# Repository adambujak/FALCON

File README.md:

FALCON

# An attempt at making drone
With Devin Bell ([@devinbellll](https://github.com/devinbellll) - Western University - Mechatronics Engineering) he's working on the flight controller, and I'm doing the RF, hardware, general bringup

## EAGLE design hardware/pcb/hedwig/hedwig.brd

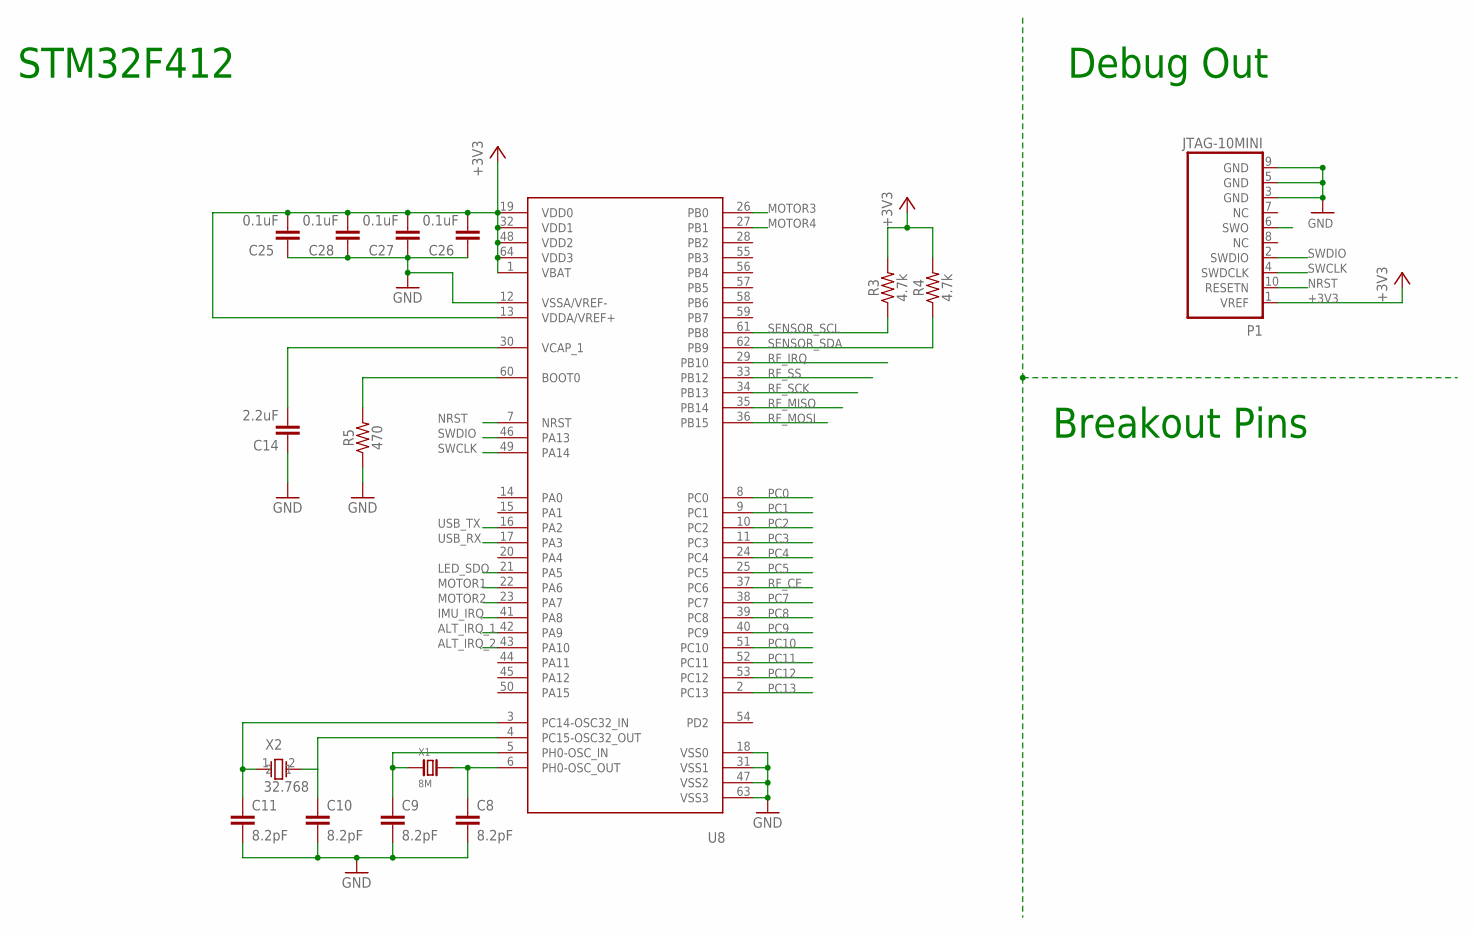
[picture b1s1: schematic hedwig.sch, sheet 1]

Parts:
C8, C9, C10, C11: 8.2pF; 0603
C14: 2.2uF; 0603
C25, C26, C27, C28: 0.1uF; 0603
P1: JTAG-10MINI
R3, R4: 4.7k; 0603
R5: 470; 0603
U8: STM32F412RE-S; QFP50P1200X1200X160-64N
X1: 8M; NDK-NX3225GD
X2: 32.768; NDK_NX3215SA-32.768K-STD-MUA-8_0

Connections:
+3V3: C25.2, C26.2, C27.2, C28.2, P1.1 (VREF), R3.2, R4.2, U8.1 (VBAT), U8.13 (VDDA/VREF+), U8.19 (VDD0), U8.32 (VDD1), U8.48 (VDD2), U8.64 (VDD3); also elsewhere on the board
ALT_IRQ_1: U8.42 (PA9); also elsewhere on the board
ALT_IRQ_2: U8.43 (PA10); also elsewhere on the board
GND: C8.2, C9.2, C10.2, C11.2, C14.1, C25.1, C26.1, C27.1, C28.1, P1.3 (GND), P1.5 (GND), P1.9 (GND), R5.1, U8.12 (VSSA/VREF-), U8.18 (VSS0), U8.31 (VSS1), U8.47 (VSS2), U8.63 (VSS3); also elsewhere on the board
IMU_IRQ: U8.41 (PA8); also elsewhere on the board
LED_SDO: U8.21 (PA5); also elsewhere on the board
MOTOR1: U8.22 (PA6); also elsewhere on the board
MOTOR2: U8.23 (PA7); also elsewhere on the board
MOTOR3: U8.26 (PB0); also elsewhere on the board
MOTOR4: U8.27 (PB1); also elsewhere on the board
unnamed: C9.1, U8.5 (PH0-OSC_IN), X1.1
unnamed: C8.1, U8.6 (PH0-OSC_OUT), X1.2
unnamed: C11.1, U8.3 (PC14-OSC32_IN), X2.1
unnamed: C10.1, U8.4 (PC15-OSC32_OUT), X2.2
unnamed: R5.2, U8.60 (BOOT0)
unnamed: C14.2, U8.30 (VCAP_1)
NRST: P1.10 (RESETN), U8.7 (NRST); also elsewhere on the board
PC0: U8.8 (PC0)
PC1: U8.9 (PC1)
PC2: U8.10 (PC2)
PC3: U8.11 (PC3)
PC4: U8.24 (PC4)
PC5: U8.25 (PC5)
PC7: U8.38 (PC7)
PC8: U8.39 (PC8)
PC9: U8.40 (PC9)
PC10: U8.51 (PC10)
PC11: U8.52 (PC11)
PC12: U8.53 (PC12)
PC13: U8.2 (PC13)
RF_CE: U8.37 (PC6); also elsewhere on the board
RF_IRQ: U8.29 (PB10); also elsewhere on the board
RF_MISO: U8.35 (PB14); also elsewhere on the board
RF_MOSI: U8.36 (PB15); also elsewhere on the board
RF_SCK: U8.34 (PB13); also elsewhere on the board
RF_SS: U8.33 (PB12); also elsewhere on the board
SENSOR_SCL: R3.1, U8.61 (PB8); also elsewhere on the board
SENSOR_SDA: R4.1, U8.62 (PB9); also elsewhere on the board
SWCLK: P1.4 (SWDCLK), U8.49 (PA14)
SWDIO: P1.2 (SWDIO), U8.46 (PA13)
USB_RX: U8.17 (PA3); also elsewhere on the board
USB_TX: U8.16 (PA2); also elsewhere on the board

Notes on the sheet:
Breakout Pins
STM32F412
Debug Out

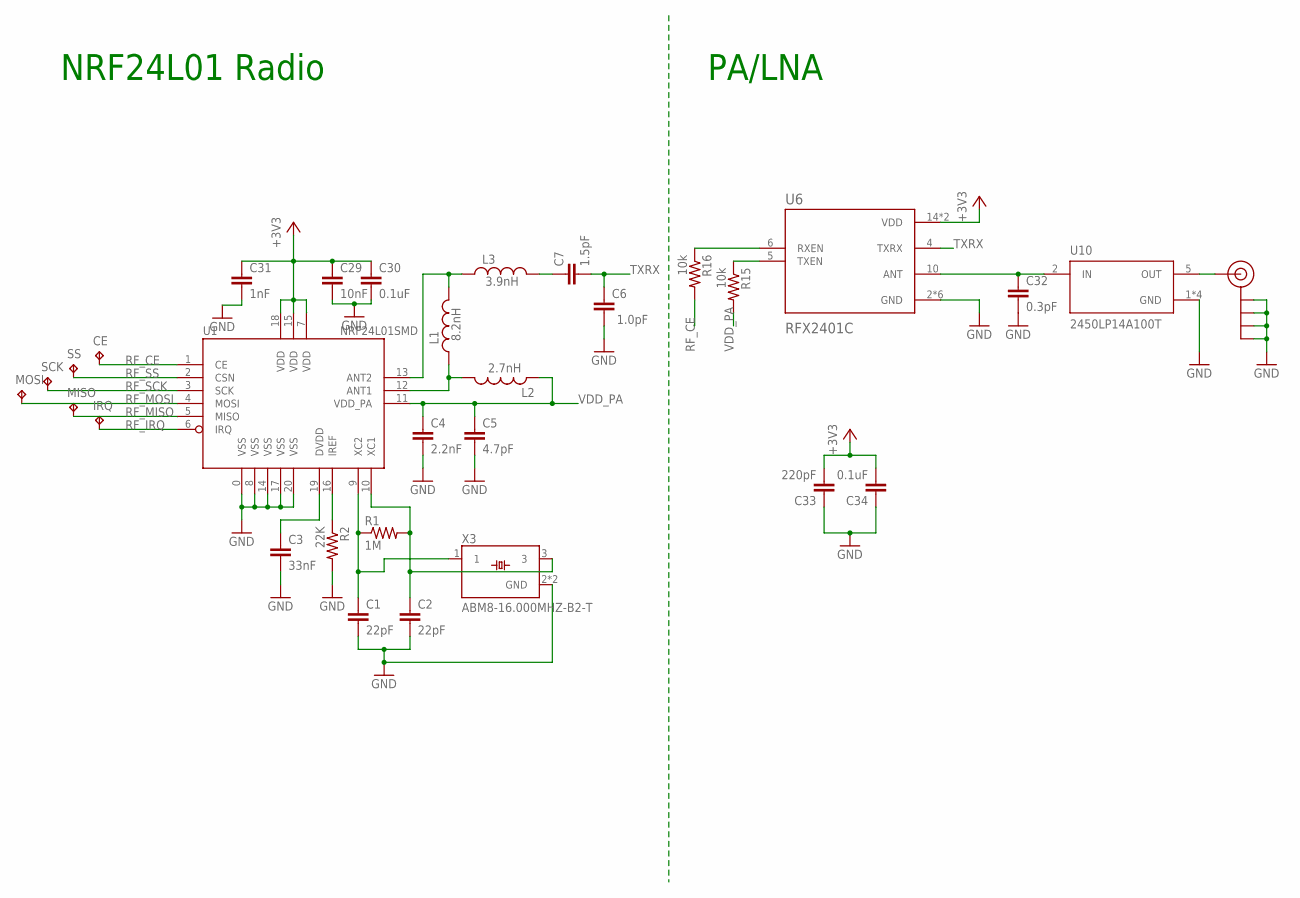
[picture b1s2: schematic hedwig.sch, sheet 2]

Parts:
C1, C2: 22pF; C0402
C3: 33nF; C0402
C4: 2.2nF; C0402
C5: 4.7pF; C0402
C6: 1.0pF; C0402
C7: 1.5pF; C0402
C29: 10nF; C0402
C30, C34: 0.1uF; C0402
C31: 1nF; C0402
C32: 0.3pF; C0402
C33: 220pF; C0402
CE: TPB1,27; B1,27
IRQ: TPB1,27; B1,27
J3: SMA_EDGE; SMA-EDGE
L1: 8.2nH; C0402
L2: 2.7nH; C0402
L3: 3.9nH; C0402
MISO: TPB1,27; B1,27
MOSI: TPB1,27; B1,27
R1: 1M; C0402
R2: 22K; C0402
R15, R16: 10k; C0402
SCK: TPB1,27; B1,27
SS: TPB1,27; B1,27
U1: NRF24L01SMD; QFN20
U6: RFX2401C; QFN50P300X300X60-17N
U10: 2450LP14A100T; ICCAF50P160X80X70-6N
X3: ABM8-16.000MHZ-B2-T; OSCSC320X250X100N

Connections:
+3V3: C29.1, C30.1, C31.1, C33.2, C34.2, U1.7 (VDD), U1.15 (VDD), U1.18 (VDD), U6.14 (VDD), U6.16 (VDD); also elsewhere on the board
GND: C1.2, C2.2, C3.2, C4.2, C5.2, C6.1, C29.2, C30.2, C31.2, C32.2, C33.1, C34.1, J3.GND@0 (GND), J3.GND@1 (GND), J3.GND@2 (GND), J3.GND@3 (GND), R2.2, U1.0 (VSS), U1.8 (VSS), U1.14 (VSS), U1.17 (VSS), U1.20 (VSS), U6.2 (GND), U6.3 (GND), U6.8 (GND), U6.9 (GND), U6.11 (GND), U6.17 (GND), U10.1 (GND), U10.3 (GND), U10.4 (GND), U10.6 (GND), X3.2 (GND), X3.4 (GND); also elsewhere on the board
unnamed: C1.1, R1.1, U1.9 (XC2), X3.1
unnamed: C2.1, R1.2, U1.10 (XC1), X3.3
unnamed: L1.1, L2.2, U1.12 (ANT1)
unnamed: R2.1, U1.16 (IREF)
unnamed: C3.1, U1.19 (DVDD)
unnamed: L1.2, L3.1, U1.13 (ANT2)
unnamed: C7.1, L3.2
unnamed: C32.1, U6.10 (ANT), U10.2 (IN)
unnamed: J3.SIG (SIGNAL), U10.5 (OUT)
unnamed: R16.1, U6.6 (RXEN)
unnamed: R15.1, U6.5 (TXEN)
RF_CE: CE.TP, R16.2, U1.1 (CE); also elsewhere on the board
RF_IRQ: IRQ.TP, U1.6 (IRQ); also elsewhere on the board
RF_MISO: MISO.TP, U1.5 (MISO); also elsewhere on the board
RF_MOSI: MOSI.TP, U1.4 (MOSI); also elsewhere on the board
RF_SCK: SCK.TP, U1.3 (SCK); also elsewhere on the board
RF_SS: SS.TP, U1.2 (CSN); also elsewhere on the board
TXRX: C6.2, C7.2, U6.4 (TXRX)
VDD_PA: C4.1, C5.1, L2.1, R15.2, U1.11 (VDD_PA)

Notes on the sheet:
NRF24L01 Radio
PA/LNA

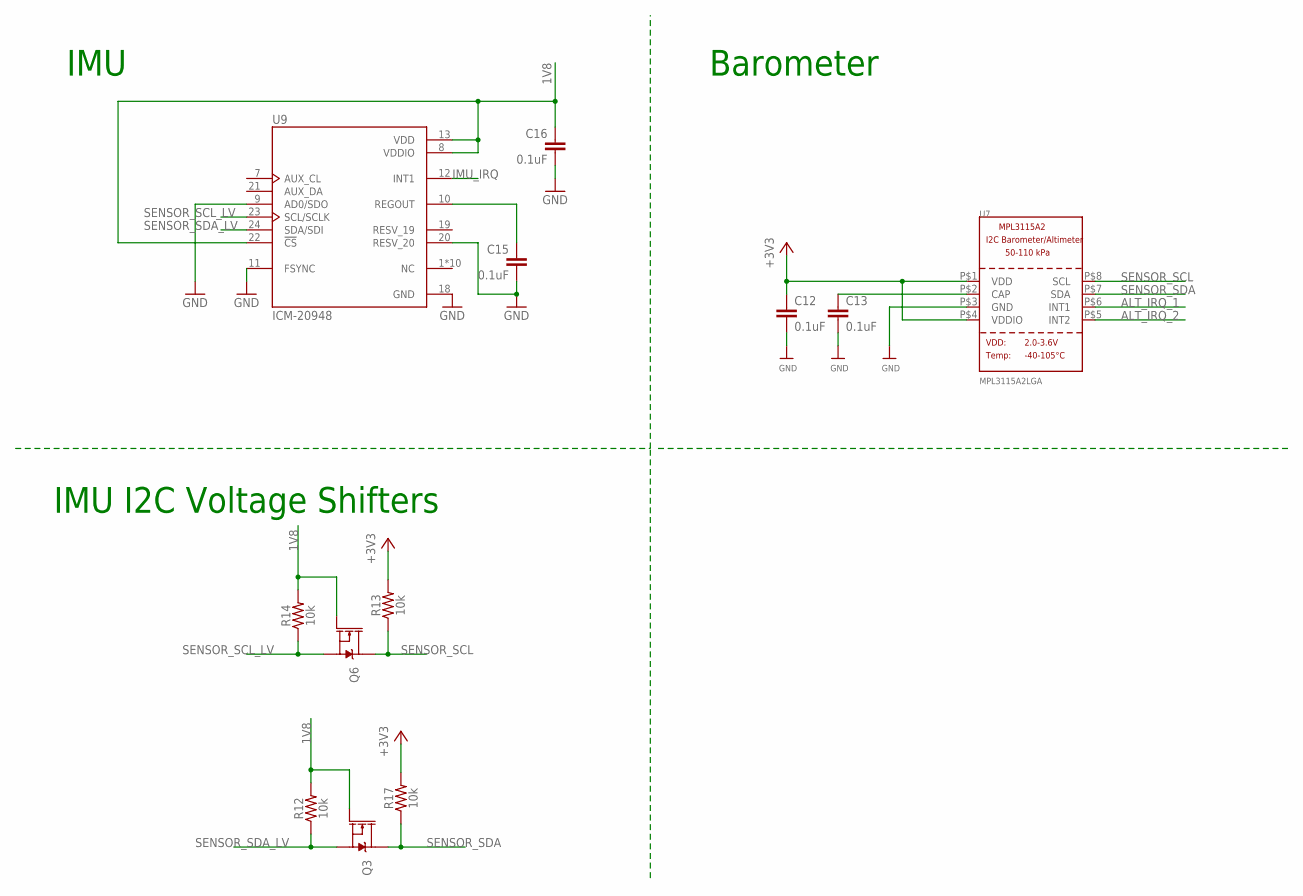
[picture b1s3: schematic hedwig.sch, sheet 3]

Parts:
C12, C13: 0.1uF; 0603
C15, C16: 0.1uF; 0603-CAP
Q3, Q6: 20V/0.2A/8MHz/1.2Ω/1Vth; SOT-416FL
R12, R13, R14, R17: 10k; 0603
U7: MPL3115A2LGA; LGA8
U9: ICM-20948; QFN40P300X300X105-24N

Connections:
1V8: C16.1, Q3.1 (G), Q6.1 (G), R12.2, R14.2, U9.8 (VDDIO), U9.13 (VDD), U9.22 (!CS); also elsewhere on the board
+3V3: C12.1, R13.2, R17.2, U7.P$1 (VDD), U7.P$4 (VDDIO); also elsewhere on the board
ALT_IRQ_1: U7.P$6 (INT1); also elsewhere on the board
ALT_IRQ_2: U7.P$5 (INT2); also elsewhere on the board
CAP: C13.1, U7.P$2 (CAP)
GND: C12.2, C13.2, C15.2, C16.2, U7.P$3 (GND), U9.9 (AD0/SDO), U9.11 (FSYNC), U9.18 (GND), U9.20 (RESV_20); also elsewhere on the board
IMU_IRQ: U9.12 (INT1); also elsewhere on the board
unnamed: C15.1, U9.10 (REGOUT)
SENSOR_SCL: Q6.3 (D), R13.1, U7.P$8 (SCL); also elsewhere on the board
SENSOR_SCL_LV: Q6.2 (S), R14.1, U9.23 (SCL/SCLK)
SENSOR_SDA: Q3.3 (D), R17.1, U7.P$7 (SDA); also elsewhere on the board
SENSOR_SDA_LV: Q3.2 (S), R12.1, U9.24 (SDA/SDI)

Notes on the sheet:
IMU
Barometer
IMU I2C Voltage Shifters

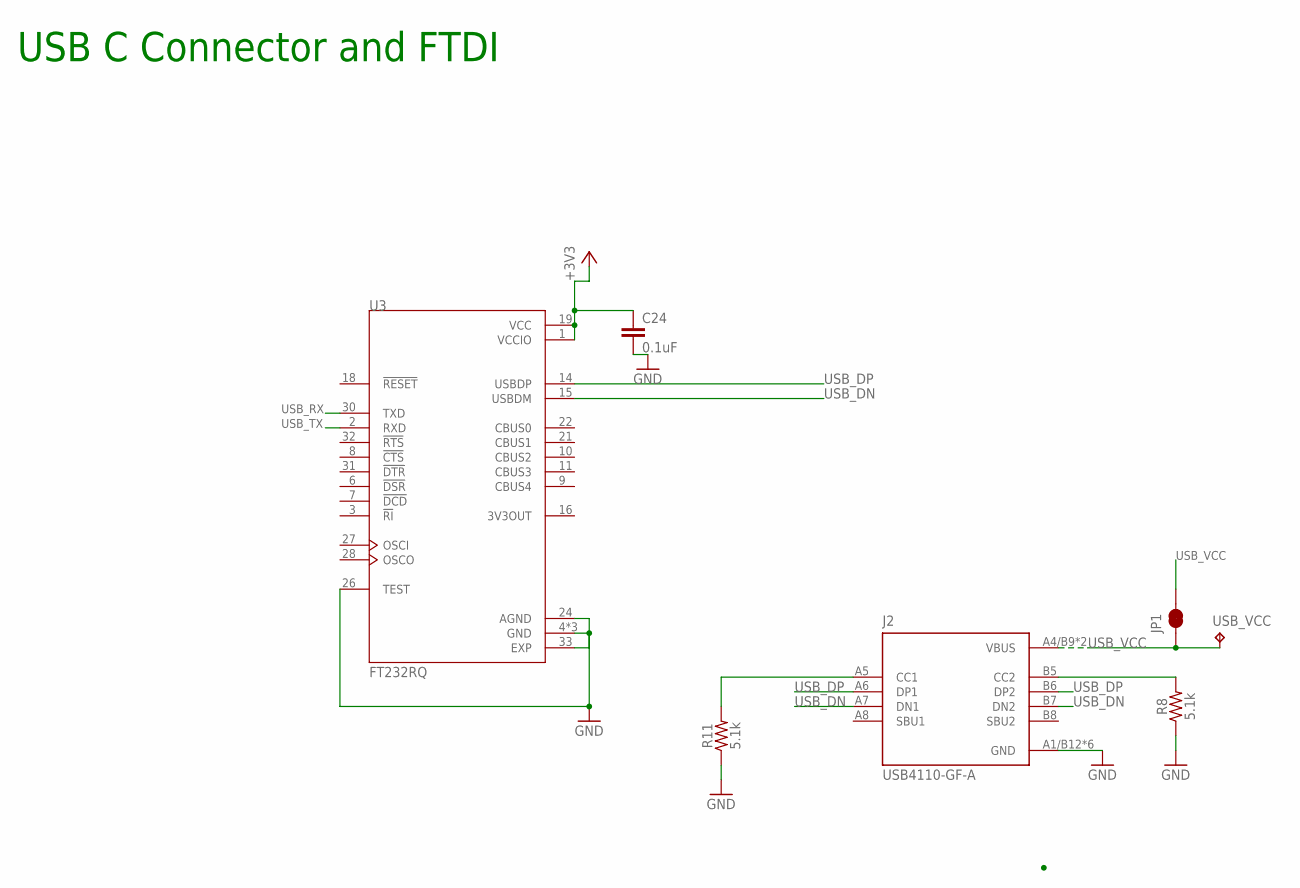
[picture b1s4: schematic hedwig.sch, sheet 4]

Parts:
C24: 0.1uF; 0603
J2: USB4110-GF-A; GCT_USB4110-GF-A
JP1: JUMPER-SMT_2_NC_TRACE_SILK; SMT-JUMPER_2_NC_TRACE_SILK
R8, R11: 5.1k; 0603
U3: FT232RQ; QFN50P500X500X90-33N
USB_VCC: TPB2,54; B2,54

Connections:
+3V3: C24.1, U3.1 (VCCIO), U3.19 (VCC); also elsewhere on the board
GND: C24.2, J2.A1/B12 (GND), J2.B1/A12 (GND), J2.S1 (GND), J2.S2 (GND), J2.S3 (GND), J2.S4 (GND), R8.1, R11.1, U3.4 (GND), U3.17 (GND), U3.20 (GND), U3.24 (AGND), U3.26 (TEST), U3.33 (EXP); also elsewhere on the board
unnamed: J2.B5 (CC2), R8.2
unnamed: J2.A5 (CC1), R11.2
USB_DN: J2.A7 (DN1), J2.B7 (DN2), U3.15 (USBDM)
USB_DP: J2.A6 (DP1), J2.B6 (DP2), U3.14 (USBDP)
USB_RX: U3.30 (TXD); also elsewhere on the board
USB_TX: U3.2 (RXD); also elsewhere on the board
USB_VCC: J2.A4/B9 (VBUS), J2.B4/A9 (VBUS), JP1.1, JP1.2, USB_VCC.TP; also elsewhere on the board

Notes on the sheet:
USB C Connector and FTDI

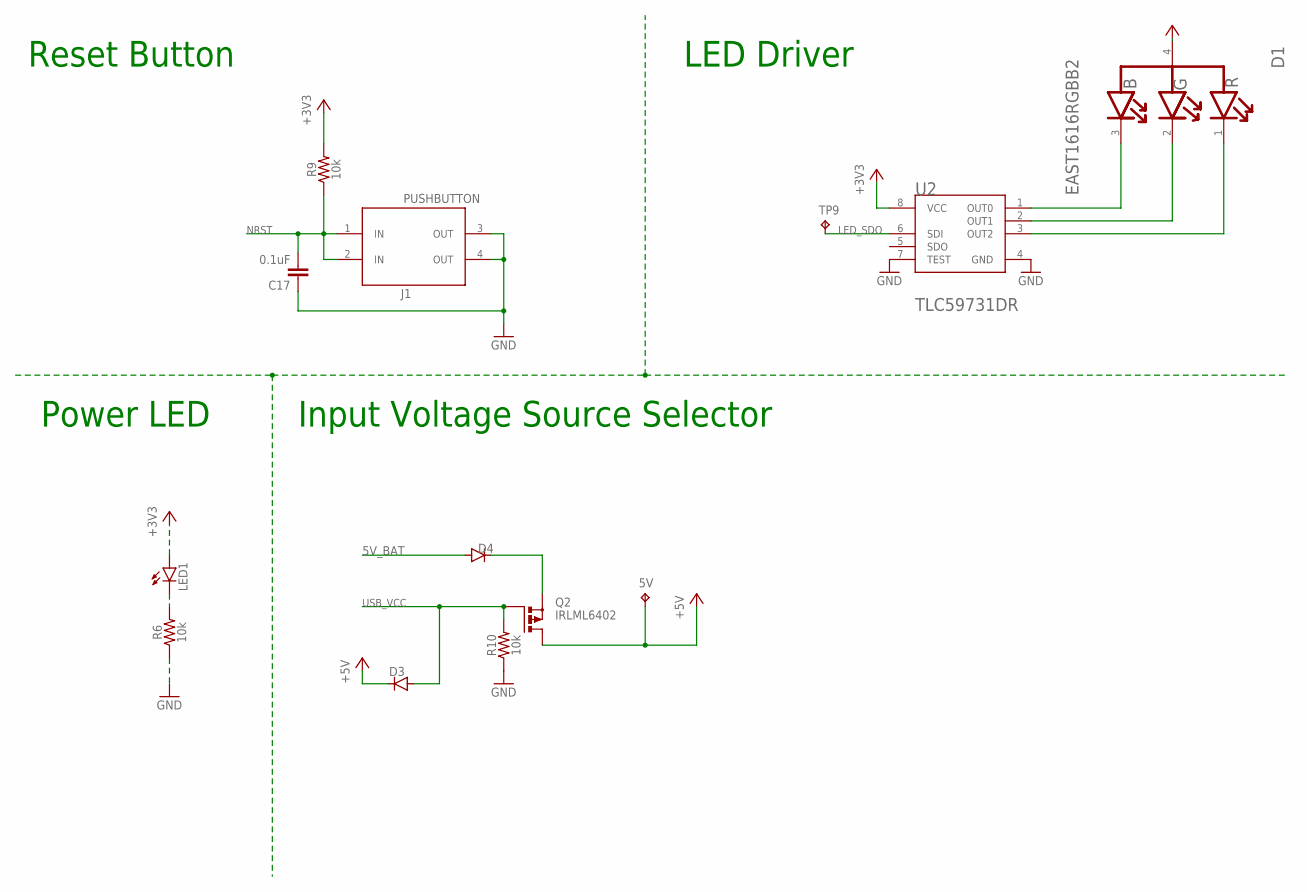
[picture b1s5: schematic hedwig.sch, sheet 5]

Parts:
5V: TPB2,54; B2,54
C17: 0.1uF; 0603
D1: EVERLIGHT_EAST1616RGBB2EVERLIGHT_EAST1616RGBB2_0_0; EVERLIGHT_EAST1616RGBB2_0
D3, D4: DIODE_0603
J1: PUSHBUTTON; PUSH_BUTTON
LED1: LEDCHIPLED_1206; CHIPLED_1206
Q2: IRLML6402; SOT-23
R6, R9, R10: 10k; 0603
TP9: TPB1,27; B1,27
U2: TEXAS_INSTRUMENTS_TLC59731DRTEXAS_INSTRUMENTS_TLC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; TEXAS_INSTRUMENTS_TLC59731DR_0

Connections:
5V_BAT: D4.A; also elsewhere on the board
+3V3: D1.4 (COMMON_ANODE), LED1.A, R9.2, U2.8 (VCC); also elsewhere on the board
+5V: 5V.TP, D3.C, Q2.P3 (D); also elsewhere on the board
GND: C17.1, J1.3 (OUT), J1.4 (OUT), R6.1, R10.1, U2.4 (GND), U2.7 (TEST); also elsewhere on the board
LED_SDO: TP9.TP, U2.6 (SDI); also elsewhere on the board
unnamed: D1.1 (RED_CATHODE), U2.3 (OUT2)
unnamed: D1.3 (BLUE_CATHODE), U2.1 (OUT0)
unnamed: LED1.C, R6.2
unnamed: D1.2 (GREEN_CATHODE), U2.2 (OUT1)
unnamed: D4.C, Q2.P2 (S)
NRST: C17.2, J1.1 (IN), J1.2 (IN), R9.1; also elsewhere on the board
USB_VCC: D3.A, Q2.P1 (G), R10.2; also elsewhere on the board

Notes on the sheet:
Reset Button
LED Driver
Power LED
Input Voltage Source Selector

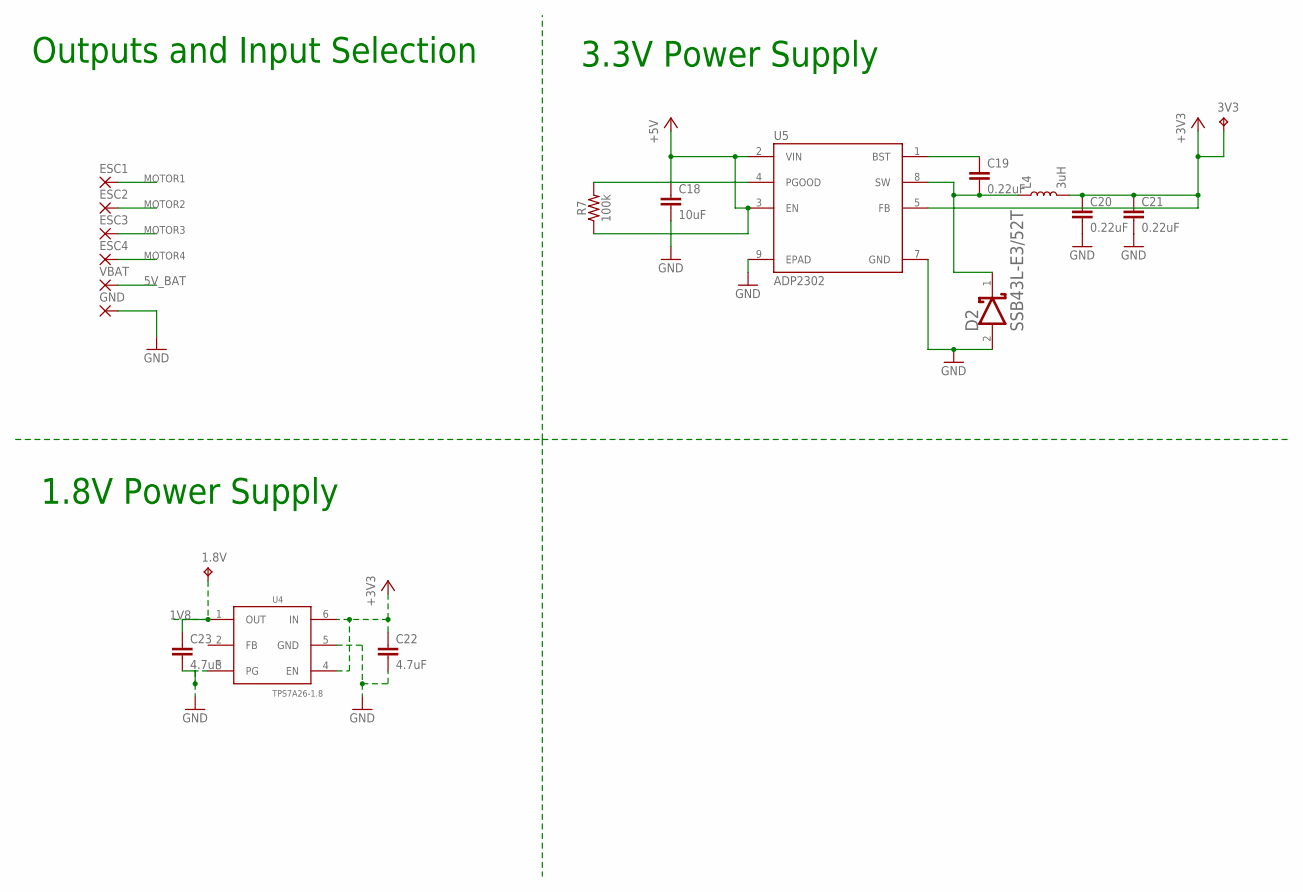
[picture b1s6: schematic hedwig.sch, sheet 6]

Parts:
1.8V, 3V3: TPB2,54; B2,54
C18: 10uF; 0603
C19, C20, C21: 0.22uF; 0603
C22, C23: 4.7uF; 0603
D2: SSB43L; VISHAY_SSB43L-E3-52T_0
ESC1, ESC2, ESC3, ESC4: SMD2; SMD1,27-2,54
GND: 2,54/1,0
L4: 3uH; REG_INDUCTOR
R7: 100k; 0603
U4: TPS7A26-1.8; WSON
U5: ADP2302; SOIC127P600X175-9N
VBAT: 2,54/1,0

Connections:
1V8: 1.8V.TP, C23.1, U4.1 (OUT); also elsewhere on the board
5V_BAT: VBAT.1; also elsewhere on the board
+3V3: 3V3.TP, C20.1, C21.1, C22.1, L4.@2 (2), U4.4 (EN), U4.6 (IN), U5.5 (FB); also elsewhere on the board
+5V: C18.1, R7.1, U5.2 (VIN), U5.3 (EN); also elsewhere on the board
GND: C18.2, C20.2, C21.2, C22.2, C23.2, D2.2 (ANODE), GND.1, U4.3 (PG), U4.5 (GND), U5.7 (GND), U5.9 (EPAD); also elsewhere on the board
MOTOR1: ESC1.1; also elsewhere on the board
MOTOR2: ESC2.1; also elsewhere on the board
MOTOR3: ESC3.1; also elsewhere on the board
MOTOR4: ESC4.1; also elsewhere on the board
unnamed: C19.1, U5.1 (BST)
unnamed: R7.2, U5.4 (PGOOD)
unnamed: C19.2, D2.1 (CATHODE), L4.@1 (1), U5.8 (SW)

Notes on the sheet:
Outputs and Input Selection
3.3V Power Supply
1.8V Power Supply

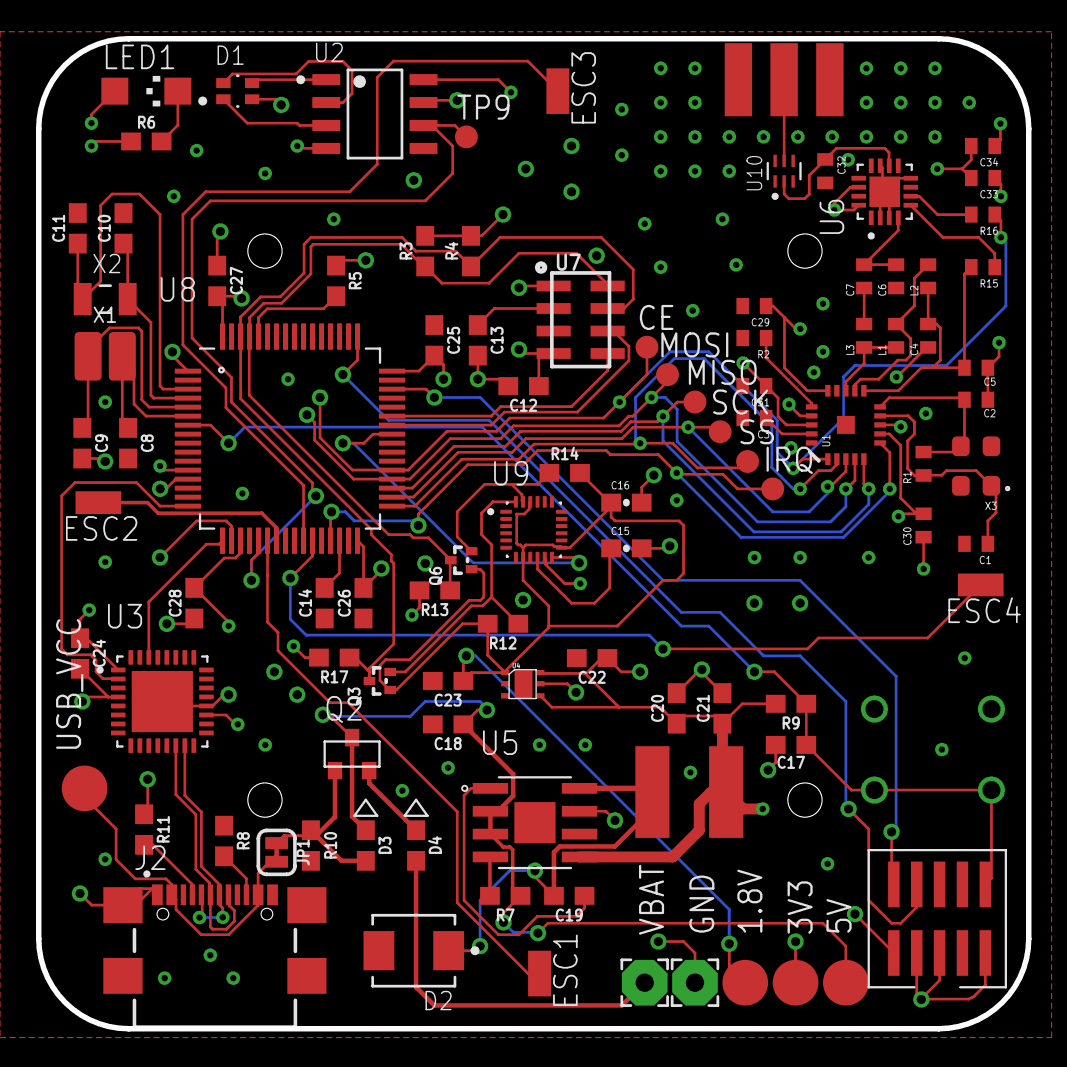
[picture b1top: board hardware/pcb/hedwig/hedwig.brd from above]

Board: 4 copper layers, 55.0 x 55.0 mm, 98 parts (0 on the bottom side), 62 nets.

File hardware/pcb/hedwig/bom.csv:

Parts,Device,Package,Value,Quantity,Digi-Key Part Number
"C1, C2",CAPACITOR,0402,22pF,2,720-1593-1-ND
"C12, C13, C15, C16, C17, C25, C26, C27, C28",CAPACITOR,0603,0.1uF,2,1276-6985-1-ND
C14,CAPACITOR,0603,2.2uF,1,1276-6726-1-ND
C18,CAPACITOR,0603,10uF,1,490-10475-1-ND
"C19, C20, C21",CAPACITOR,0603,0.22uF,3,311-3103-1-ND
"C22, C23",CAPACITOR,0603,4.7uF,2,445-13231-1-ND
C24,CAPACITOR,0603,0.1uF,1,445-13231-1-ND
C29,CAPACITOR,0402,10nF,1,1276-1051-1-ND
C3,CAPACITOR,0402,33nF,1,490-11149-1-ND
"C30, C34",CAPACITOR,0402,0.1uF,2,587-1994-1-ND
C31,CAPACITOR,0402,1nF,1,587-1051-1-ND
C32,CAPACITOR,0402,0.3pF,1,399-6155-1-ND
C33,CAPACITOR,0402,220pF,1,311-3060-1-ND
C4,CAPACITOR,0402,2.2nF,1,587-4324-1-ND
C5,CAPACITOR,0402,4.7pF,1,1276-6694-1-ND
C6,CAPACITOR,0402,1.0pF,1,587-5103-1-ND
C7,CAPACITOR,0402,1.5pF,1,587-5122-1-ND
"C8, C9, C10, C11",CAPACITOR,0603,8.2pF,4,490-12727-1-ND
D1,EVERLIGHT_EAST1616RGBB2EVERLIGHT_EAST1616RGBB2_0_0,CUSTOM,,1,1080-1551-1-ND
D2,VISHAY_SSB43L-E3-52TVISHAY_SSB43L-E3-52T_0_0,CUSTOM,,1,SSB43L-E3/52TGICT-ND
"D3, D4",DIODE_0603,0603,,2,CCS15S30L3FCT-ND
J1,PUSHBUTTON,CUSTOM,,1,2449-CT11025.0F160-ND
J2,USB4110-GF-A,CUSTOM,,1,2073-USB4110-GF-A-1-ND
J3,SMA_EDGE,SMA_EDGE,,1,CONREVSMA003.062-G-ND
L1,INDUCTOR0402,0402,8.2nH,1,2035-0402HP-8N2EHTSCT-ND
L2,INDUCTOR0402,0402,2.7nH,1,2035-0402HP-2N7EDTSCT-ND
L3,INDUCTOR0402,0402,3.9nH,1,2035-0402HP-3N9EDTSCT-ND
L4,INDUCTOR3V3,CUSTOM,3uH,1,445-173052-1-ND
LED1,LEDCHIPLED_1206,1206,,1,MP-3014-1100-35-80
P1,JTAG-10MINI,JTAG-10MINI,,1,SAM8799-ND
Q2,MOSFTET-PCH-IRLML6402,SOT-23,,1,SI2305-TPMSCT-ND
"Q3, Q6",MOSFET-NCH-RE1C002UN,SOT-416FL,,2,RE1C002UNTCLCT-ND
R1,RESISTOR,0402,1M,1,2037-PFR05S-105-FNHCT-ND
"R6, R9, R10, R12, R13, R14, R17",RESISTOR,0603,10k,5,RNCP0603FTD10K0CT-ND
"R15, R16",RESISTOR,0402,10k,2,RNCF0402BTE10K0CT-ND
R2,RESISTOR,0402,22K,1,RMCF0402FT22K0CT-ND
"R3, R4",RESISTOR,0603,4.7k,2,MCT0603-4.7K-MDCT-ND
R5,RESISTOR,0603,470,1,RMCF0603FT470RCT-ND
R7,RESISTOR,0603,100k,1,RMCF0603FT100KCT-ND
"R8, R11",RESISTOR,0603,5.1k,2,RMCF0603FT5K10CT-ND
U1,NRF24L01SMD,QFN20,,1,1490-NRF24L01P-RCT-ND
U2,TLC59731DR,,,1,296-40590-1-ND
U3,FT232RQ,QFN50-33N,,1,768-1307-ND
U4,TPS7A26-1.8,WSON,,1,296-TPS7A2618DRVRCT-ND
U5,ADP2302,SOIC127-9N,,1,ADP2302ARDZ-3.3-R7CT-ND
U6,RFX2401C,QFN500-17N,,1,863-1828-1-ND
U7,MPL3115A2LGA,LGA8,,1,MPL3115A2R1CT-ND
U8,STM32F412RE-S,QFP50-64N,,1,497-19350-1-ND
U9,ICM-20948,QFN40-24N,,1,1428-1123-1-ND
U10,2450LP14A100T,ICCAF50-6N,,1,712-1129-1-ND
X1,CRYSTAL-NX3225GD,NDK-NX3225GD,8MHz,1,644-1178-2-ND
X2,NX32,NDK_NX3215SA-32.768K-STD-MUA-8_0,32.768kHz,1,644-1156-1-ND
X3,ABM8-16.000MHZ-B2-T,OSCSC320X250X100N,16MHz,1,535-9134-1-ND

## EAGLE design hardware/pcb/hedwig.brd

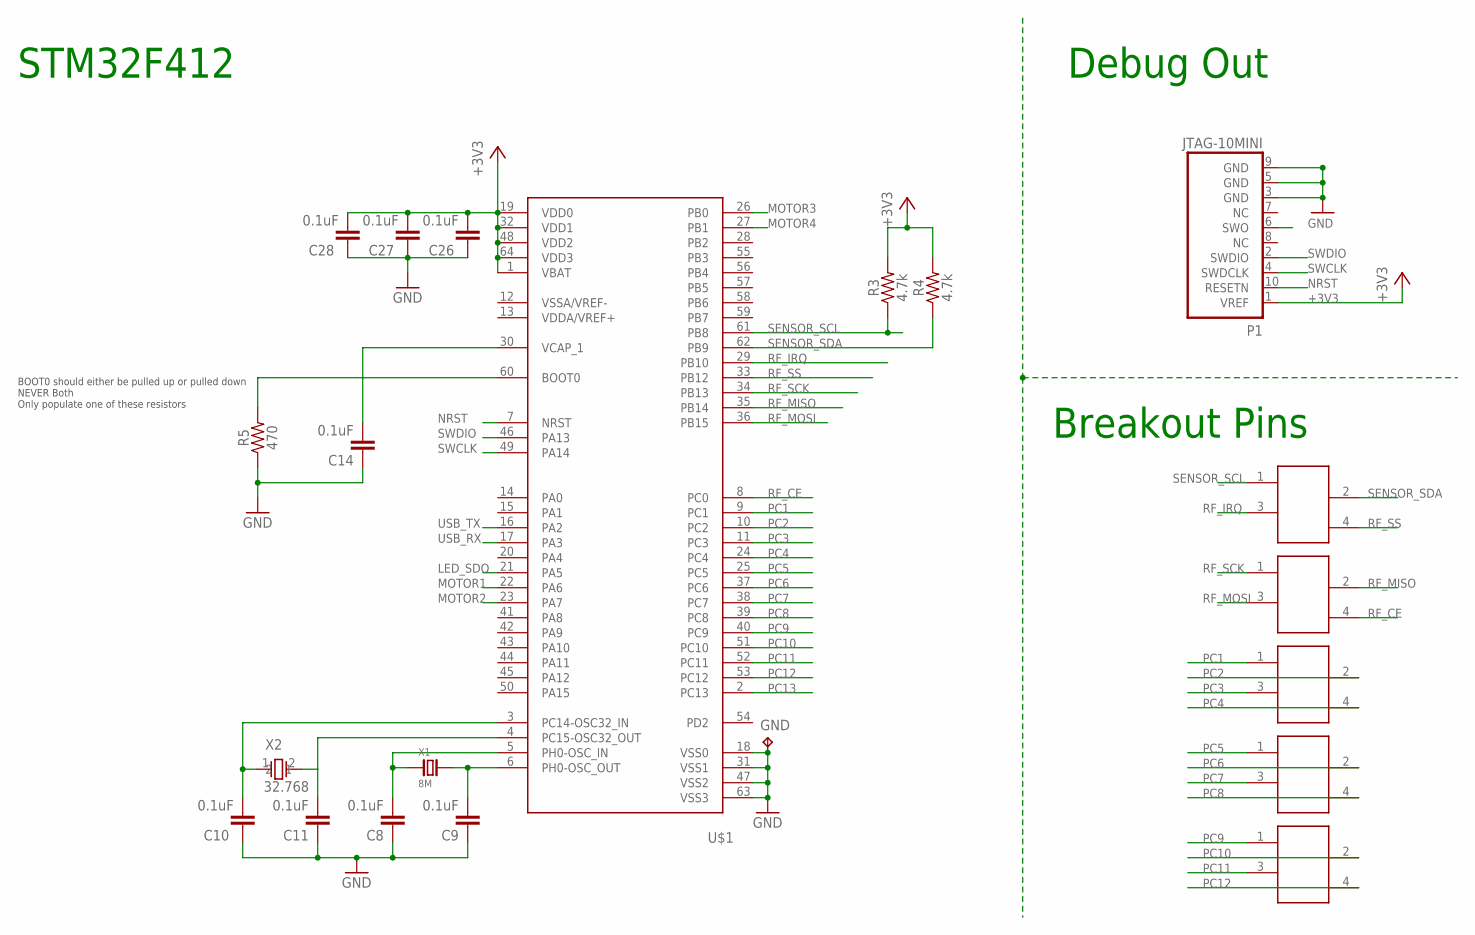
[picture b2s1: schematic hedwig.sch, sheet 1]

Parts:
C8, C9, C10, C11, C14, C26, C27, C28: 0.1uF; 0603
GND: TPB2,54; B2,54
P1: JTAG-10MINI
P2: SENSOR_SCL; STAGGERED-CONNECTOR
P3: RF_SCK; STAGGERED-CONNECTOR
P4: PC1; STAGGERED-CONNECTOR
P5: PC5; STAGGERED-CONNECTOR
P6: PC9; STAGGERED-CONNECTOR
R3, R4: 4.7k; 0603
R5: 470; 0603
U$1: STM32F412RE-S; QFP50P1200X1200X160-64N
X1: 8M; NDK-NX3225GD
X2: 32.768; NDK_NX3215SA-32.768K-STD-MUA-8_0

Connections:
+3V3: C26.2, C27.2, C28.2, P1.1 (VREF), R3.2, R4.2, U$1.1 (VBAT), U$1.19 (VDD0), U$1.32 (VDD1), U$1.48 (VDD2), U$1.64 (VDD3); also elsewhere on the board
GND: C8.1, C9.1, C10.1, C11.1, C14.1, C26.1, C27.1, C28.1, GND.TP, P1.3 (GND), P1.5 (GND), P1.9 (GND), R5.1, U$1.18 (VSS0), U$1.31 (VSS1), U$1.47 (VSS2), U$1.63 (VSS3); also elsewhere on the board
LED_SDO: U$1.21 (PA5); also elsewhere on the board
MOTOR1: U$1.22 (PA6); also elsewhere on the board
MOTOR2: U$1.23 (PA7); also elsewhere on the board
MOTOR3: U$1.26 (PB0); also elsewhere on the board
MOTOR4: U$1.27 (PB1); also elsewhere on the board
unnamed: C8.2, U$1.5 (PH0-OSC_IN), X1.1
unnamed: C9.2, U$1.6 (PH0-OSC_OUT), X1.2
unnamed: C10.2, U$1.3 (PC14-OSC32_IN), X2.1
unnamed: C11.2, U$1.4 (PC15-OSC32_OUT), X2.2
unnamed: R5.2, U$1.60 (BOOT0)
unnamed: C14.2, U$1.30 (VCAP_1)
NRST: P1.10 (RESETN), U$1.7 (NRST); also elsewhere on the board
PC1: P4.1, U$1.9 (PC1)
PC2: P4.2, U$1.10 (PC2)
PC3: P4.3, U$1.11 (PC3)
PC4: P4.4, U$1.24 (PC4)
PC5: P5.1, U$1.25 (PC5)
PC6: P5.2, U$1.37 (PC6)
PC7: P5.3, U$1.38 (PC7)
PC8: P5.4, U$1.39 (PC8)
PC9: P6.1, U$1.40 (PC9)
PC10: P6.2, U$1.51 (PC10)
PC11: P6.3, U$1.52 (PC11)
PC12: P6.4, U$1.53 (PC12)
PC13: U$1.2 (PC13)
RF_CE: P3.4, U$1.8 (PC0); also elsewhere on the board
RF_IRQ: P2.3, U$1.29 (PB10); also elsewhere on the board
RF_MISO: P3.2, U$1.35 (PB14); also elsewhere on the board
RF_MOSI: P3.3, U$1.36 (PB15); also elsewhere on the board
RF_SCK: P3.1, U$1.34 (PB13); also elsewhere on the board
RF_SS: P2.4, U$1.33 (PB12); also elsewhere on the board
SENSOR_SCL: P2.1, R3.1, U$1.61 (PB8); also elsewhere on the board
SENSOR_SDA: P2.2, R4.1, U$1.62 (PB9); also elsewhere on the board
SWCLK: P1.4 (SWDCLK), U$1.49 (PA14)
SWDIO: P1.2 (SWDIO), U$1.46 (PA13)
USB_RX: U$1.17 (PA3); also elsewhere on the board
USB_TX: U$1.16 (PA2); also elsewhere on the board

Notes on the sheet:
BOOT0 should either be pulled up or pulled down NEVER Both Only populate one of these resistors
Breakout Pins
STM32F412
Debug Out

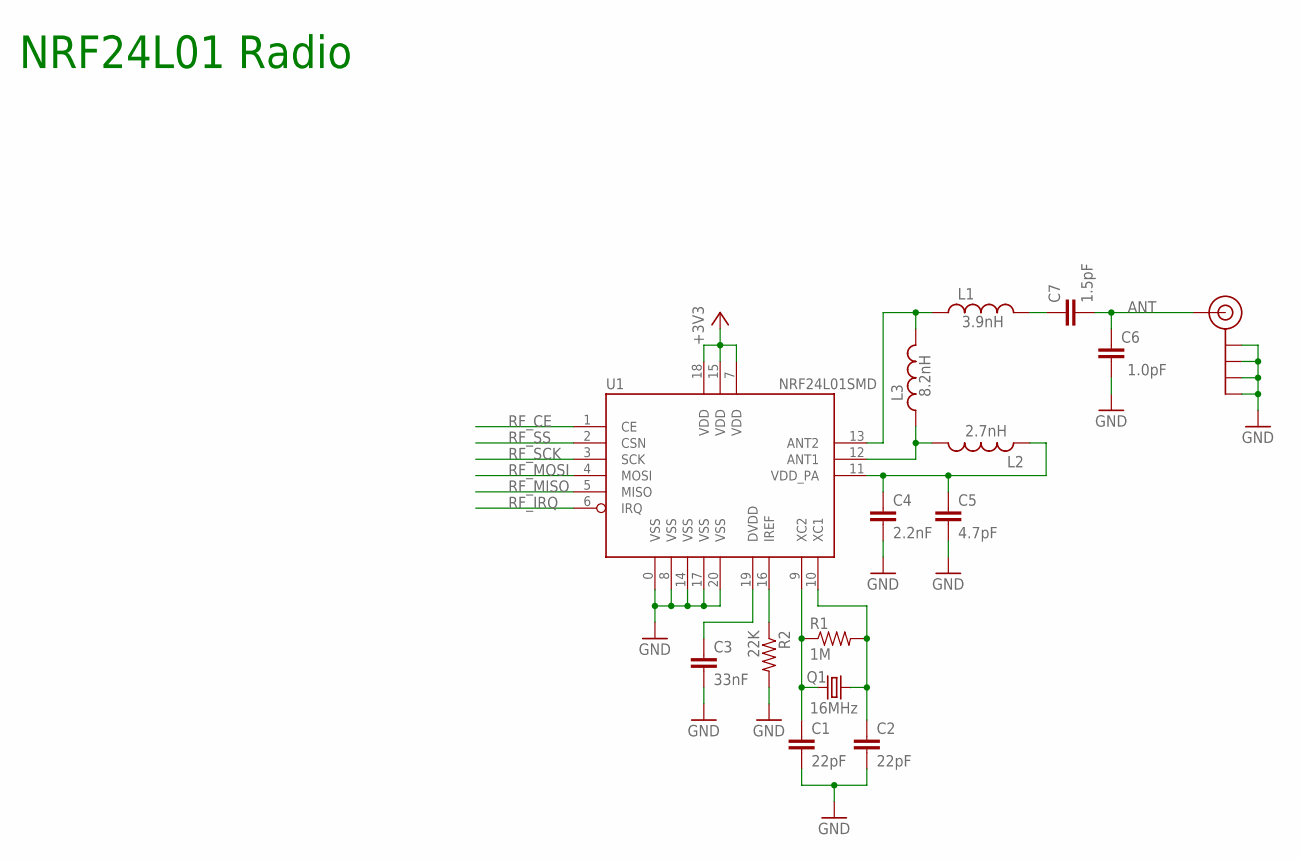
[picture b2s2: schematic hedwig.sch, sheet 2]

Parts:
C1, C2: 22pF; C0402
C3: 33nF; C0402
C4: 2.2nF; C0402
C5: 4.7pF; C0402
C6: 1.0pF; C0402
C7: 1.5pF; C0402
J$1: SMA_EDGE; SMA-EDGE
L1: 3.9nH; C0402
L2: 2.7nH; C0402
L3: 8.2nH; C0402
Q1: 16MHz; CRYSTAL-SMD-5X3
R1: 1M; C0402
R2: 22K; C0402
U1: NRF24L01SMD; QFN20

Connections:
+3V3: U1.7 (VDD), U1.15 (VDD), U1.18 (VDD); also elsewhere on the board
ANT: C6.2, C7.2, J$1.SIG (SIGNAL)
GND: C1.2, C2.2, C3.2, C4.2, C5.2, C6.1, J$1.GND@0 (GND), J$1.GND@1 (GND), J$1.GND@2 (GND), J$1.GND@3 (GND), R2.2, U1.0 (VSS), U1.8 (VSS), U1.14 (VSS), U1.17 (VSS), U1.20 (VSS); also elsewhere on the board
unnamed: C1.1, Q1.1, R1.1, U1.9 (XC2)
unnamed: C2.1, Q1.3 (2), R1.2, U1.10 (XC1)
unnamed: L2.2, L3.1, U1.12 (ANT1)
unnamed: R2.1, U1.16 (IREF)
unnamed: C3.1, U1.19 (DVDD)
unnamed: L1.1, L3.2, U1.13 (ANT2)
unnamed: C4.1, C5.1, L2.1, U1.11 (VDD_PA)
unnamed: C7.1, L1.2
RF_CE: U1.1 (CE); also elsewhere on the board
RF_IRQ: U1.6 (IRQ); also elsewhere on the board
RF_MISO: U1.5 (MISO); also elsewhere on the board
RF_MOSI: U1.4 (MOSI); also elsewhere on the board
RF_SCK: U1.3 (SCK); also elsewhere on the board
RF_SS: U1.2 (CSN); also elsewhere on the board

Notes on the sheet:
NRF24L01 Radio

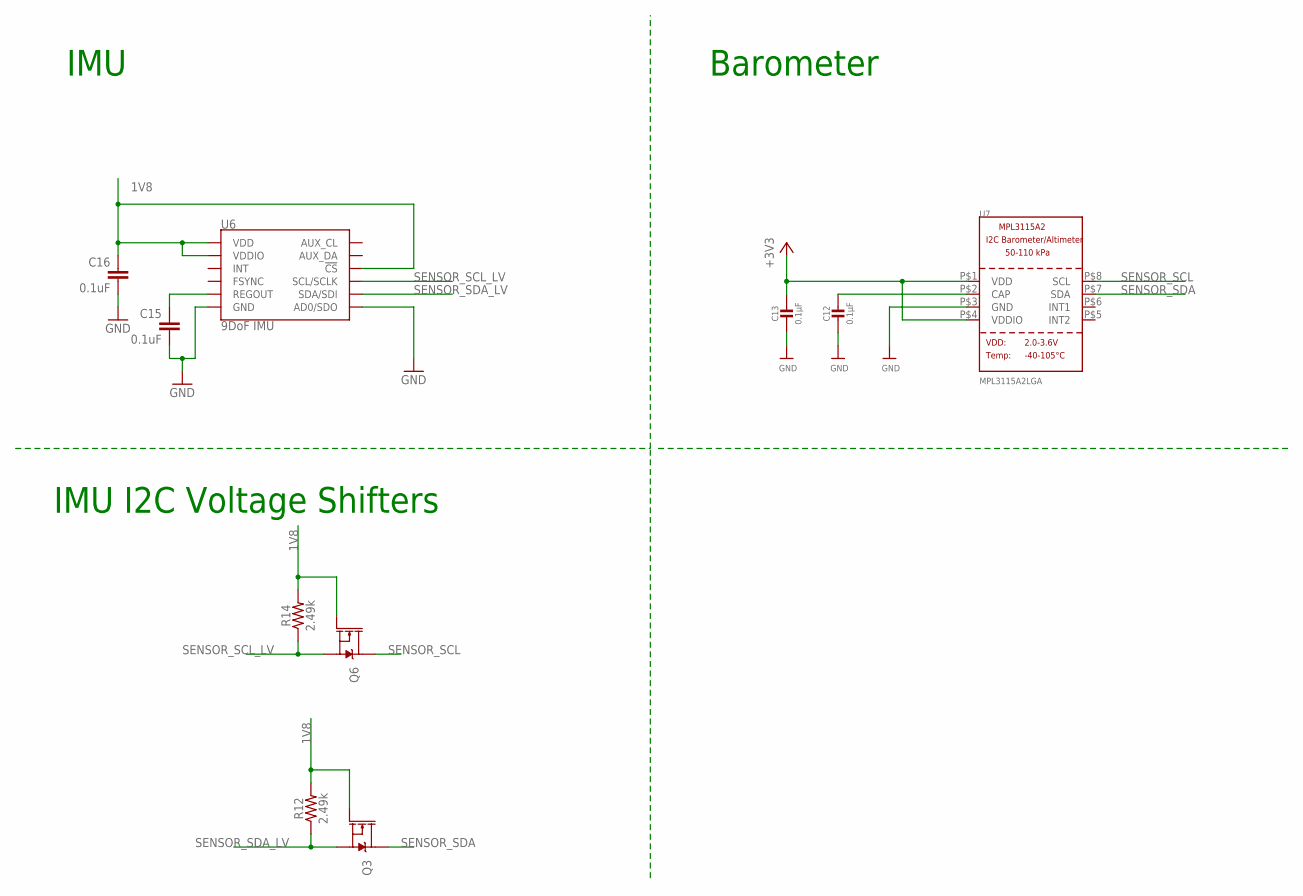
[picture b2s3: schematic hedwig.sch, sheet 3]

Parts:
C12, C13: 0.1µF; 0805-NO
C15, C16: 0.1uF; 0603-CAP
Q3, Q6: 20V/0.2A/8MHz/1.2Ω/1Vth; SOT-416FL
R12, R14: 2.49k; 0603
U6: 9DoF IMU; QFN24-3X3
U7: MPL3115A2LGA; LGA8

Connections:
1V8: C16.1, Q3.1 (G), Q6.1 (G), R12.2, R14.2, U6.8 (VDDIO), U6.13 (VDD), U6.22 (!CS); also elsewhere on the board
+3V3: C13.1, U7.P$1 (VDD), U7.P$4 (VDDIO); also elsewhere on the board
ADSD_STUB: U6.9 (AD0/SDO)
CAP: C12.1, U7.P$2 (CAP)
GND: C12.2, C13.2, C15.2, C16.2, U6.18 (GND), U6.20 (GND), U7.P$3 (GND); also elsewhere on the board
REGOUT: C15.1, U6.10 (REGOUT)
SENSOR_SCL: Q6.3 (D), U7.P$8 (SCL); also elsewhere on the board
SENSOR_SCL_LV: Q6.2 (S), R14.1, U6.23 (SCL/SCLK)
SENSOR_SDA: Q3.3 (D), U7.P$7 (SDA); also elsewhere on the board
SENSOR_SDA_LV: Q3.2 (S), R12.1, U6.24 (SDA/SDI)

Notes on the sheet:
IMU
Barometer
IMU I2C Voltage Shifters

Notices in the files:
parts and their libraries:
SparkFun-Capacitors: Licensing: Creative Commons ShareAlike 4.0 International - https://creativecommons.org/licenses/by-sa/4.0
